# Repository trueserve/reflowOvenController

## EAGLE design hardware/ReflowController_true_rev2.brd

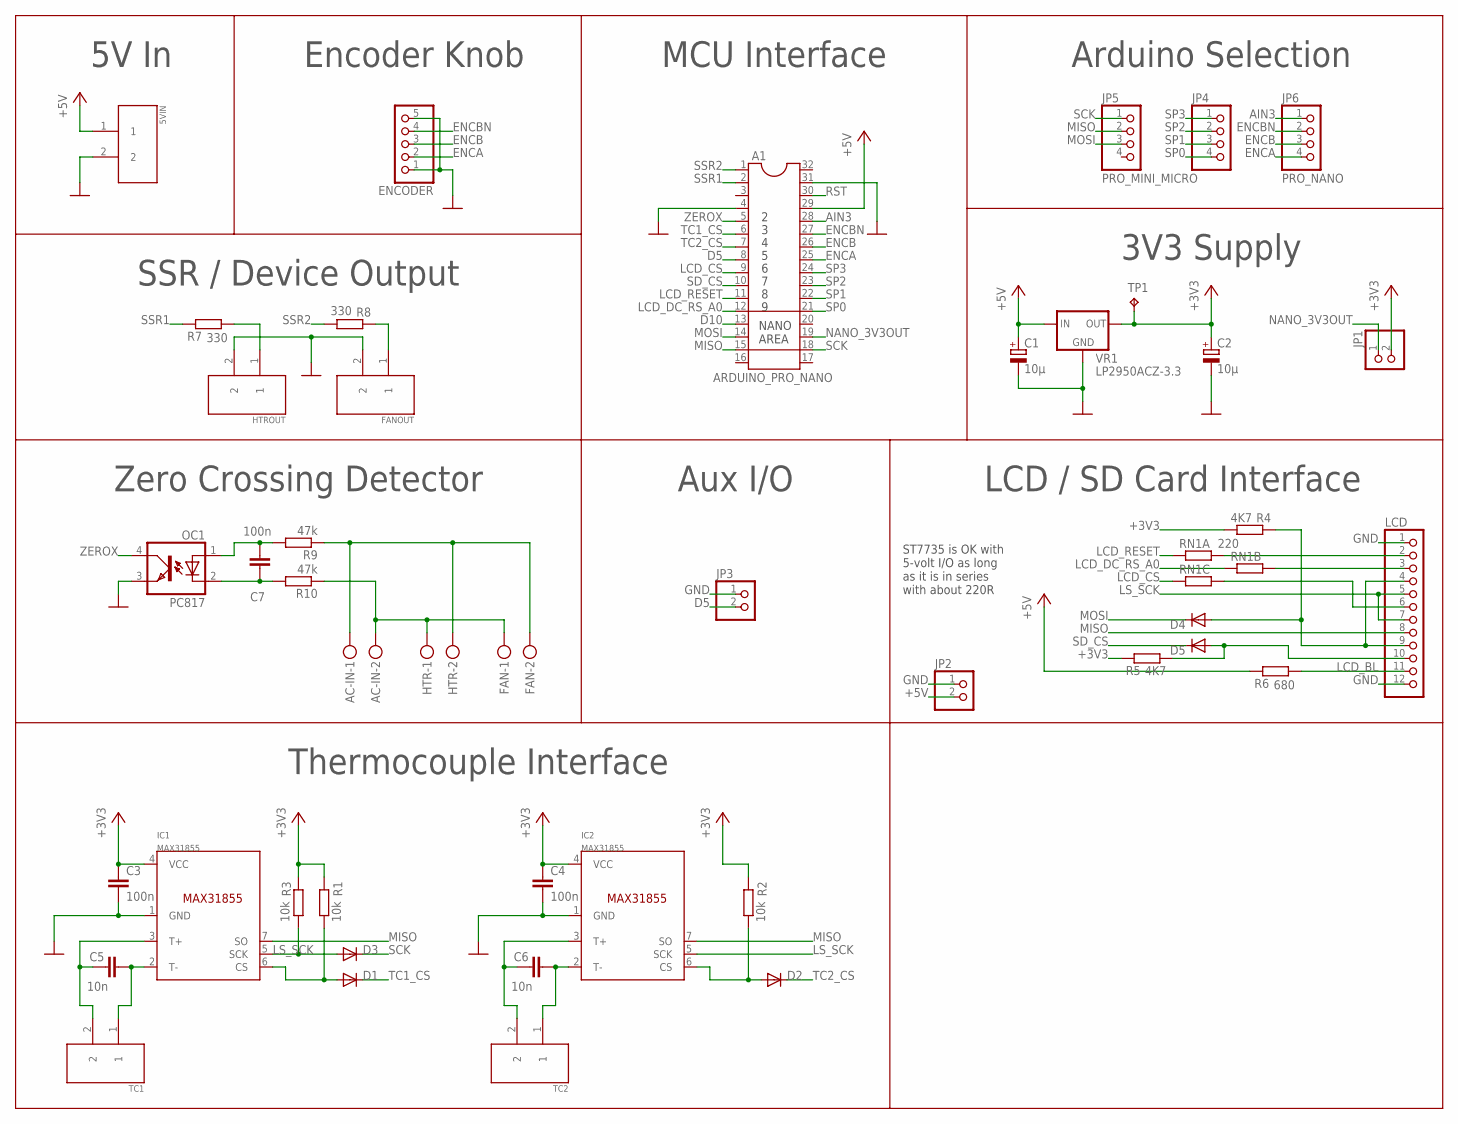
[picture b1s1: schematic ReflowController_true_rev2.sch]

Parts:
5VIN: WECO_110-M-221/2; WECO-PHOENIXTERM-2-POS
A1: ARDUINO_PRO_NANO; DIL32
AC-IN: MKDSN1,5/2-5,08
C1, C2: 10µ; C/6032-28R
C3, C4: 100n; C0805
C5, C6: 10n; C0805
C7: 100n; C150-054X183
D1, D2, D3, D4, D5: DIODESOD-123; SOD-123
ENCODER: PINHD-1X5; 1X05
FAN: MKDSN1,5/2-5,08
FANOUT: WECO_110-M-221/2; WECO-PHOENIXTERM-2-POS
HTR: MKDSN1,5/2-5,08
HTROUT: WECO_110-M-221/2; WECO-PHOENIXTERM-2-POS
IC1, IC2: MAX31855; SOIC8
JP1, JP2, JP3: PINHD-1X2; 1X02
JP4: PINHD-1X4RND; 1X04_RND
JP5: PRO_MINI_MICRO; 1X04_RND
JP6: PRO_NANO; 1X04_RND
LCD: PINHD-1X12; 1X12
OC1: PC817; DIL04
R1, R2, R3: 10k; R0805
R4, R5: 4K7; R0805
R6: 680; R0805
R7, R8: 330; R0805
R9, R10: 47k; 0207/5V
RN1: 220; RN8P-4R-CRA06S
TC1, TC2: WECO_110-M-221/2; WECO-PHOENIXTERM-2-POS
TP1: TPTP08R; TP08R
VR1: LP2950ACZ-3.3; TO92

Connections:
+3V3: C2.+, C3.1, C4.1, IC1.4 (VCC), IC2.4 (VCC), JP1.2, R1.2, R2.2, R3.2, R4.1, R5.2, TP1.TP, VR1.1 (OUT)
+5V: 5VIN.1, A1.29, C1.+, JP2.2, R6.2, VR1.3 (IN)
AC1: AC-IN.1, FAN.2, HTR.2, R9.1
AC2: AC-IN.2, FAN.1, HTR.1, R10.1
AIN3: A1.28, JP6.1
D5: A1.8, JP3.2
D10: A1.13
ENCA: A1.25, ENCODER.2, JP6.4
ENCB: A1.26, ENCODER.3, JP6.3
ENCBN: A1.27, ENCODER.4, JP6.2
GND: 5VIN.2, A1.4, A1.31, C1.-, C2.-, C3.2, C4.2, ENCODER.1, ENCODER.5, FANOUT.2, HTROUT.2, IC1.1 (GND), IC2.1 (GND), JP2.1, JP3.1, LCD.1, LCD.12, OC1.3 (EMIT), VR1.2 (GND)
LCD_BL: LCD.11, R6.1
LCD_CS: A1.9, RN1.3 (1)
LCD_DC_RS_A0: A1.12, RN1.2 (1)
LCD_RESET: A1.11, RN1.1
LS_MOSI: D4.A, LCD.4, LCD.9, R4.2
LS_SCK: D3.A, IC1.5 (SCK), IC2.5 (SCK), LCD.5, LCD.7, R3.1
LS_SD_CS: D5.A, LCD.10, R5.1
MISO: A1.15, IC1.7 (SO), IC2.7 (SO), JP5.2, LCD.8
MOSI: A1.14, D4.C, JP5.3
unnamed: C5.2, IC1.2 (T-), TC1.1
unnamed: C6.2, IC2.2 (T-), TC2.1
unnamed: C6.1, IC2.3 (T+), TC2.2
unnamed: LCD.3, RN1.7 (2)
unnamed: LCD.6, RN1.6 (2)
unnamed: C7.2, OC1.1 (A), R9.2
unnamed: LCD.2, RN1.8 (2)
unnamed: C7.1, OC1.2 (C), R10.2
unnamed: C5.1, IC1.3 (T+), TC1.2
unnamed: D2.A, IC2.6 (CS), R2.1
unnamed: D1.A, IC1.6 (CS), R1.1
NANO_3V3OUT: A1.19, JP1.1
RST: A1.30
SCK: A1.18, D3.C, JP5.1
SD_CS: A1.10, D5.C
SP0: A1.21, JP4.4
SP1: A1.22, JP4.3
SP2: A1.23, JP4.2
SP3: A1.24, JP4.1
SSR1: A1.2, R7.2
SSR1OUT: HTROUT.1, R7.1
SSR2: A1.1, R8.1
SSR2_OUT: FANOUT.1, R8.2
TC1_CS: A1.6, D1.C
TC2_CS: A1.7, D2.C
ZEROX: A1.5, OC1.4 (COL)

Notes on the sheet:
NANO AREA
MCU Interface
Arduino Selection
3V3 Supply
5V In
Encoder Knob
LCD / SD Card Interface
SSR / Device Output
Zero Crossing Detector
Aux I/O
Thermocouple Interface
ST7735 is OK with 5-volt I/O as long as it is in series with about 220R

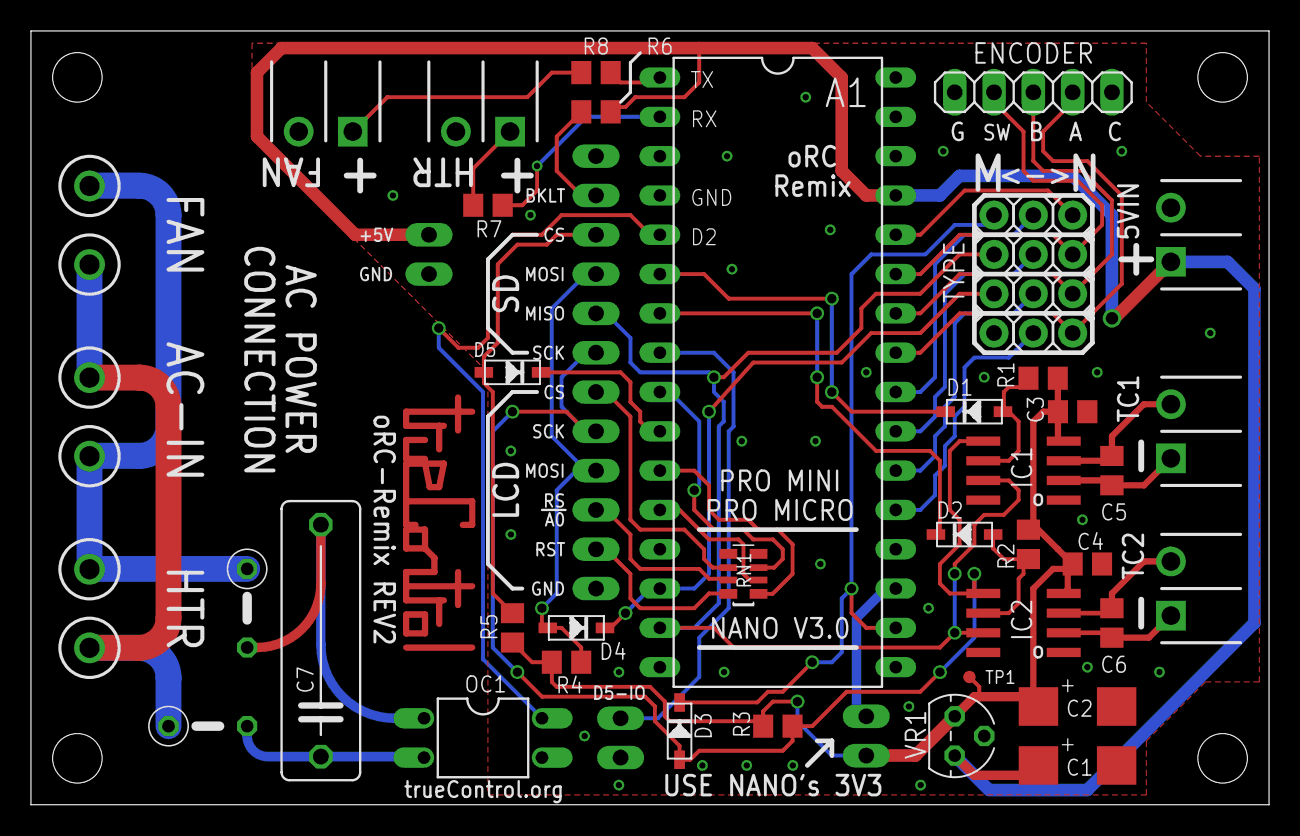
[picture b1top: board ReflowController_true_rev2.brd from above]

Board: 2 copper layers, 80.0 x 50.0 mm, 46 parts (0 on the bottom side), 44 nets.

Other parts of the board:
U$1: TC_LOGO

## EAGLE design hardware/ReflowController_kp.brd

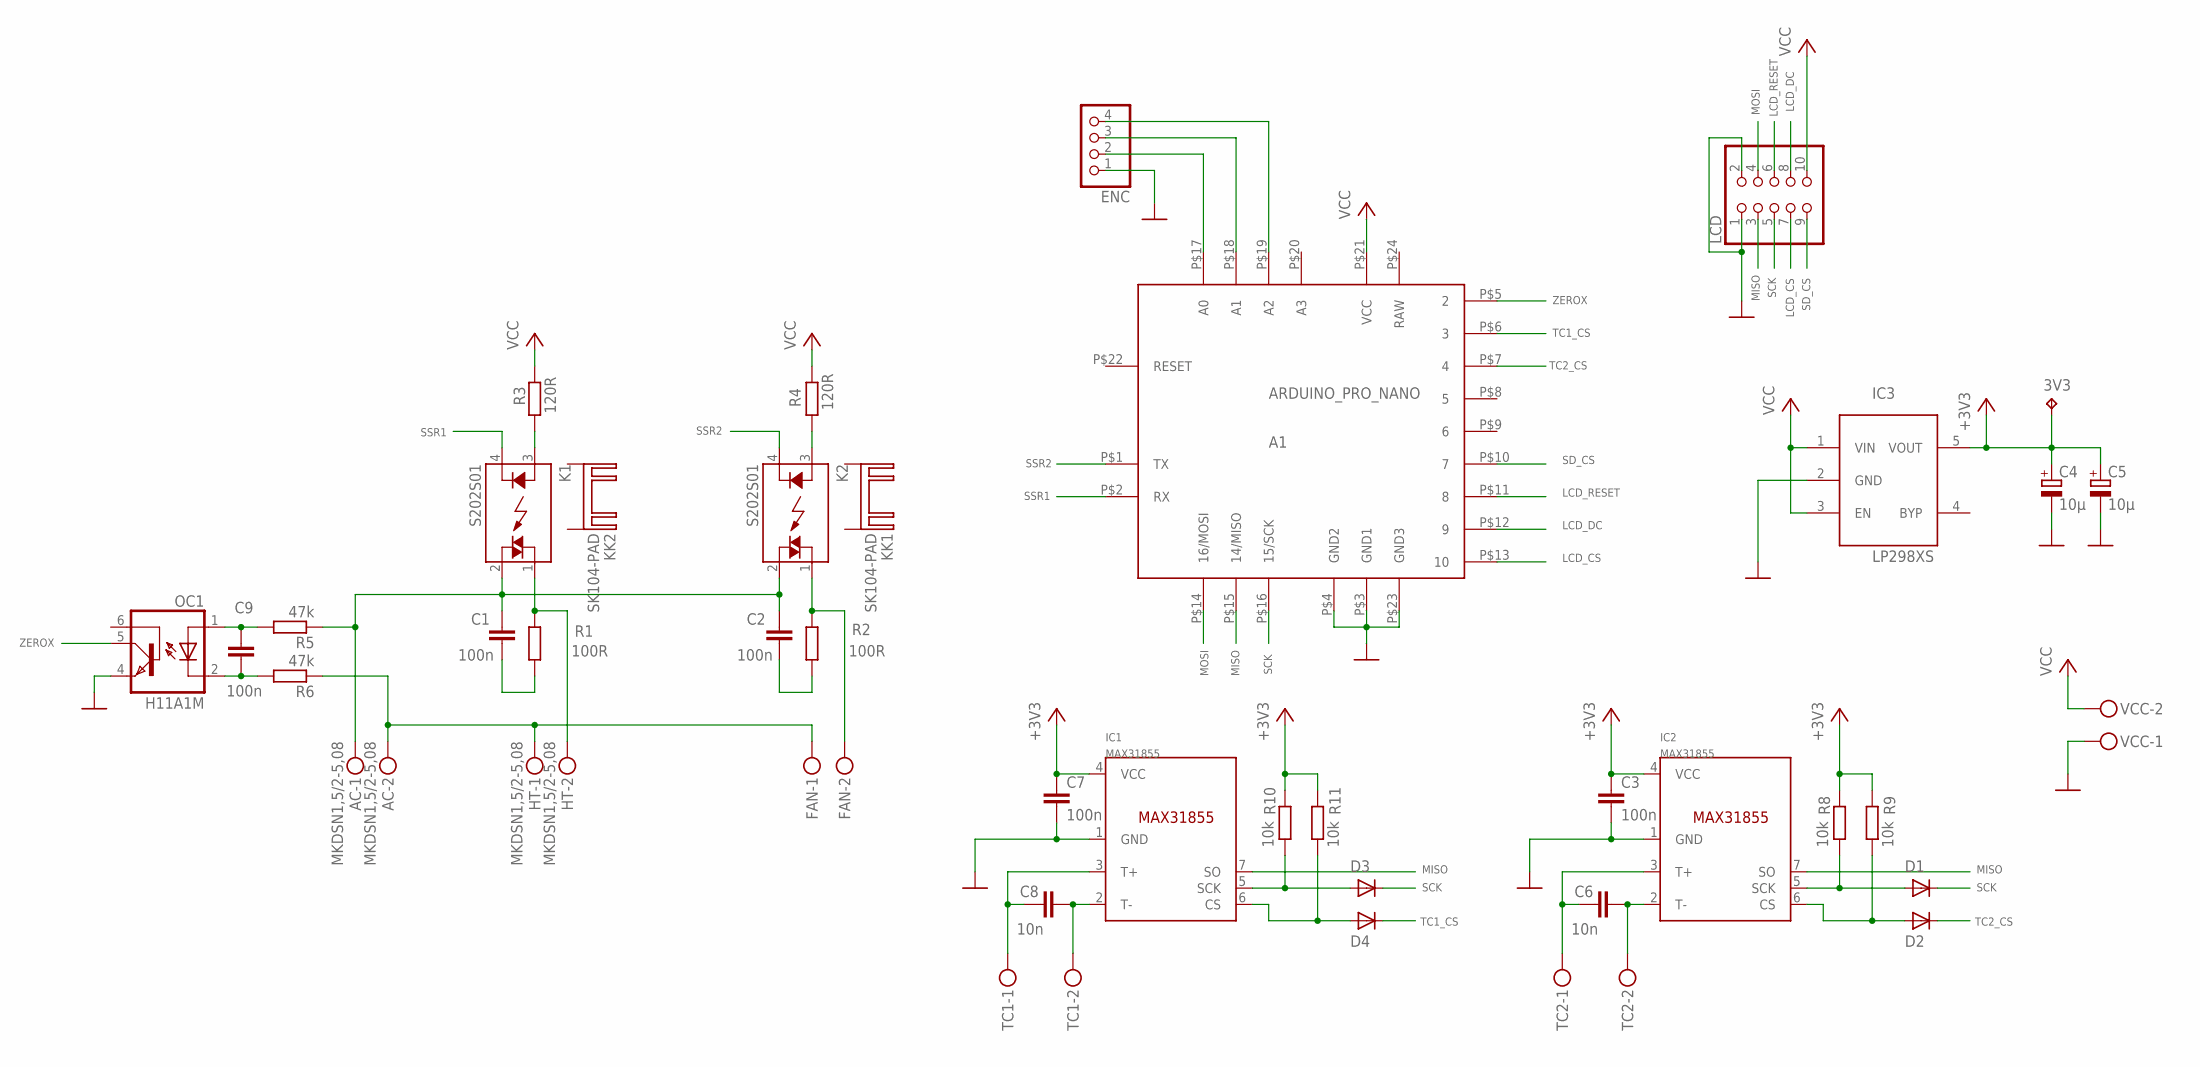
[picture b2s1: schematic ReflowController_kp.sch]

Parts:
3V3: TPTP08R; TP08R
A1: ARDUINO_PRO_NANO
AC: MKDSN1,5/2-5,08
C1, C2: 100n; XC10B5
C3, C7: 100n; C0805
C4, C5: 10µ; C/6032-28R
C6, C8: 10n; C0603
C9: 100n; C025-025X050
D1, D2, D3, D4: DIODESOD-123; SOD-123
ENC: PINHD-1X4; 1X04
FAN: MKDSN1,5/2-5,08
HT: MKDSN1,5/2-5,08
IC1, IC2: MAX31855; SOIC8
IC3: LP298XS; SOT23-5L
K1, K2: S202S01; S102S01
KK1, KK2: SK104-PAD
LCD: PINHD-2X5; 2X05
OC1: H11A1M; DIL06
R1, R2: 100R; 0207/5V
R3, R4: 120R; R0603
R5, R6: 47k; 0207/5V
R8, R9, R10, R11: 10k; R0603
TC1, TC2: MKDSN1,5/2-5,08
VCC: MKDSN1,5/2-5,08

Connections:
+3V3: 3V3.TP, C3.1, C4.+, C5.+, C7.1, IC1.4 (VCC), IC2.4 (VCC), IC3.5 (VOUT), R8.2, R9.2, R10.2, R11.2
AC1: AC.1, C1.1, C2.1, K1.2 (DS2), K2.2 (DS2), R5.1
AC2: AC.2, FAN.1, HT.1, R6.1
AC_OUT1: HT.2, K1.1 (DS1), R1.2
AC_OUT2: FAN.2, K2.1 (DS1), R2.2
GND: A1.P$3 (GND1), A1.P$4 (GND2), A1.P$23 (GND3), C3.2, C4.-, C5.-, C7.2, ENC.1, IC1.1 (GND), IC2.1 (GND), IC3.2 (GND), LCD.1, LCD.2, OC1.4 (EMI), VCC.1
LCD_CS: A1.P$13 (10), LCD.7
LCD_DC: A1.P$12 (9), LCD.8
LCD_RESET: A1.P$11 (8), LCD.6
MISO: A1.P$15 (14/MISO), IC1.7 (SO), IC2.7 (SO), LCD.3
MOSI: A1.P$14 (16/MOSI), LCD.4
unnamed: C8.2, IC1.2 (T-), TC1.2
unnamed: C6.2, IC2.2 (T-), TC2.2
unnamed: C6.1, IC2.3 (T+), TC2.1
unnamed: A1.P$17 (A0), ENC.2
unnamed: A1.P$18 (A1), ENC.3
unnamed: C1.2, R1.1
unnamed: C2.2, R2.1
unnamed: A1.P$19 (A2), ENC.4
unnamed: C9.1, OC1.1 (A), R5.2
unnamed: C9.2, OC1.2 (C), R6.2
unnamed: C8.1, IC1.3 (T+), TC1.1
unnamed: K1.3 (A), R3.2
unnamed: K2.3 (A), R4.2
unnamed: D2.A, IC2.6 (CS), R9.1
unnamed: D1.A, IC2.5 (SCK), R8.1
unnamed: D4.A, IC1.6 (CS), R11.1
unnamed: D3.A, IC1.5 (SCK), R10.1
RAW: A1.P$24 (RAW)
SCK: A1.P$16 (15/SCK), D1.C, D3.C, LCD.5
SD_CS: A1.P$10 (7), LCD.9
SSR1: A1.P$2 (RX), K1.4 (K)
SSR2: A1.P$1 (TX), K2.4 (K)
TC1_CS: A1.P$6 (3), D4.C
TC2_CS: A1.P$7 (4), D2.C
VCC: A1.P$21 (VCC), IC3.1 (VIN), IC3.3 (EN), LCD.10, R3.1, R4.1, VCC.2
ZEROX: A1.P$5 (2), OC1.5 (COL)

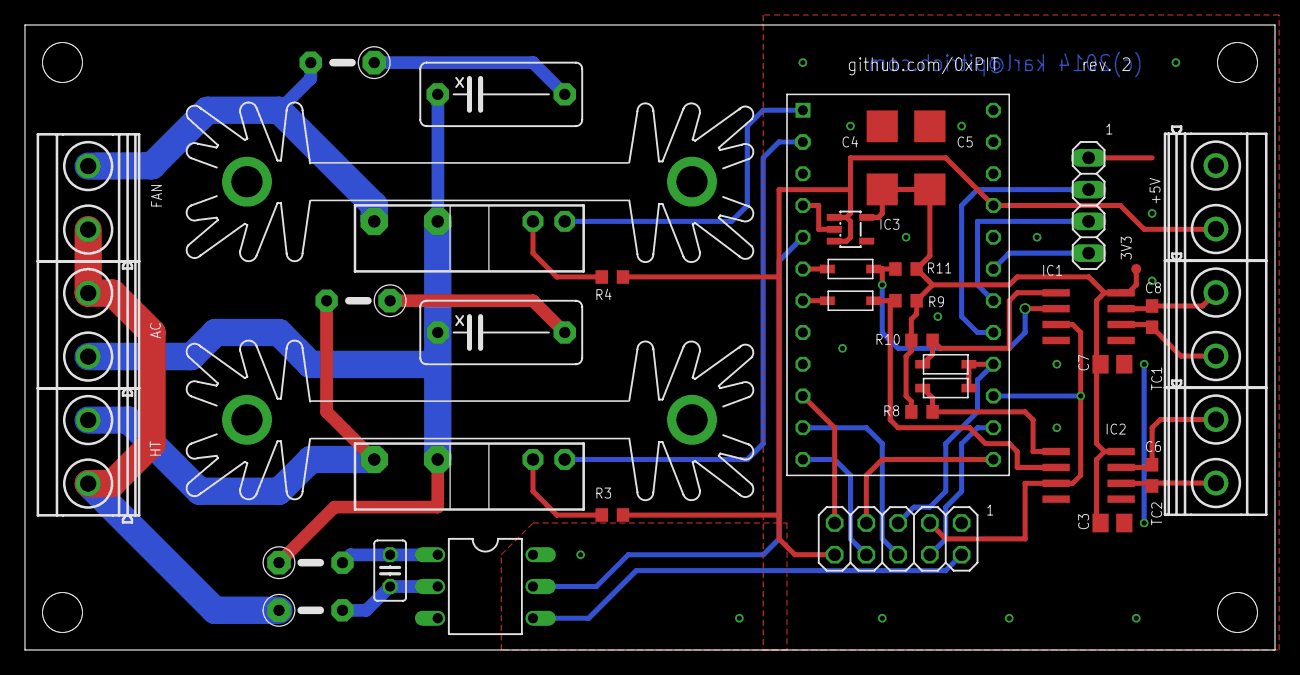
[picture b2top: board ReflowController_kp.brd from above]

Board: 2 copper layers, 100.0 x 50.0 mm, 41 parts (0 on the bottom side), 36 nets.

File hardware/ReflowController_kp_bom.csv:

Part,Value,Device,Package,Description
A1,ARDUINO_PRO_NANO,ARDUINO_PRO_NANO,ARDUINO_PRO_NANO,SparkFun Arduino Pro Nano
C1,100n,CXXC10B5,XC10B5,X CAPACITOR
C2,100n,CXXC10B5,XC10B5,X CAPACITOR
C3,100n,C-EUC0805,C0805,CAPACITOR. European symbol
C4,10µ,CPOL-EUC/6032-28R,C/6032-28R,POLARIZED CAPACITOR. European symbol
C5,10µ,CPOL-EUC/6032-28R,C/6032-28R,POLARIZED CAPACITOR. European symbol
C6,10n,C-EUC0603,C0603,CAPACITOR. European symbol
C7,100n,C-EUC0805,C0805,CAPACITOR. European symbol
C8,10n,C-EUC0603,C0603,CAPACITOR. European symbol
C9,100n,C-EU025-025X050,C025-025X050,CAPACITOR. European symbol
D1,1N4148,DIODESOD-123,SOD-123,Diode
D2,1N4148,DIODESOD-123,SOD-123,Diode
D3,1N4148,DIODESOD-123,SOD-123,Diode
D4,1N4148,DIODESOD-123,SOD-123,Diode
IC1,MAX31855,MAX31855,SOIC8,
IC2,MAX31855,MAX31855,SOIC8,
IC3,LP298XS,LP298XS,SOT23-5L,
K1,S202S01,S202S01,S102S01,Low Height Type Solid State Relays SHARP
K2,S202S01,S202S01,S102S01,Low Height Type Solid State Relays SHARP
KK1,SK104-PAD,SK104-PAD,SK104-PAD,HEATSINK manufacturer Fischer/distributor Buerklin
KK2,SK104-PAD,SK104-PAD,SK104-PAD,HEATSINK manufacturer Fischer/distributor Buerklin
OC1,H11A1M,H11A1M,DIL06,General Purpose 6-Pin Phototransistor Optocouplers
R1,100R,R-EU_0207/5V,0207/5V,RESISTOR. European symbol
R2,100R,R-EU_0207/5V,0207/5V,RESISTOR. European symbol
R3,120R,R-EU_R0603,R0603,RESISTOR. European symbol
R4,120R,R-EU_R0603,R0603,RESISTOR. European symbol
R5,47k,R-EU_0207/5V,0207/5V,RESISTOR. European symbol
R6,47k,R-EU_0207/5V,0207/5V,RESISTOR. European symbol
R8,10k,R-EU_R0603,R0603,RESISTOR. European symbol
R9,10k,R-EU_R0603,R0603,RESISTOR. European symbol
R10,10k,R-EU_R0603,R0603,RESISTOR. European symbol
R11,10k,R-EU_R0603,R0603,RESISTOR. European symbol
AC,MKDSN1.5/2-5.08,MKDSN1.5/2-5.08,MKDSN1.5/2-5.08,MKDSN 1.5/ 2-5.08 Printklemme
FAN,MKDSN1.5/2-5.08,MKDSN1.5/2-5.08,MKDSN1.5/2-5.08,MKDSN 1.5/ 2-5.08 Printklemme
HT,MKDSN1.5/2-5.08,MKDSN1.5/2-5.08,MKDSN1.5/2-5.08,MKDSN 1.5/ 2-5.08 Printklemme
TC1,MKDSN1.5/2-5.08,MKDSN1.5/2-5.08,MKDSN1.5/2-5.08,MKDSN 1.5/ 2-5.08 Printklemme
TC2,MKDSN1.5/2-5.08,MKDSN1.5/2-5.08,MKDSN1.5/2-5.08,MKDSN 1.5/ 2-5.08 Printklemme
VCC,MKDSN1.5/2-5.08,MKDSN1.5/2-5.08,MKDSN1.5/2-5.08,MKDSN 1.5/ 2-5.08 Printklemme
ENC,,PINHD-1X4,1X04,PIN HEADER
LCD,,PINHD-2X5,2X05,PIN HEADER

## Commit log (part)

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2014-10-25 Rename ReflowController.pde to ReflowController.ino
    Using extension Arduino 1.5.x GUI expects to see.
2014-10-25 Initial minor cleanup, clarification
    - Began cleaning up parts of the code and organizing sections to make it
    easier to read, no actual changes performed
    - Added ARDUINO_TYPE and BOARD_TYPE preprocessor options to configure
    the code to the target
2014-10-25 Add compile-time LCD rotation setting, usability fixes
    - Adds rotation support for LCD, and fixes text and graphics to make
    this happen
    - Adds define for rotary encoder steps at top of file
    - Fixed bug of redefine of LCD_CS in temperature.h
    - Menu items are the correct width in either rotation; editing
    - Improved splash screen, though flash size is bigger as a result
2014-10-25 Register accesses changed to Arduinoisms (portability), more clarifications
    - Minor formatting updates to fix inconsistencies and make code match
    the original programming style
    - Moved LCD physical configuration defines out of the user configurable
    area; these are set by the compile time user-configurable LCD rotation
    - Made any direct port register code no longer directly access the port
    direction and output registers. Code should be fully portable between
2014-10-26 hardware/ directory cleanup
    - Cleaned up kp's design files and documents
    - Removed kp's board house DRU, added ignore for .dru
2014-10-26 true's Reflow Controller PCB+Schematic
    My version of the Reflow Controller.
    This is REV2, untested. I have mostly tested REV1 so far. Yes, it is way
    more complicated than the original. :)
    - Schematic cleaned up and organized. Hopefully this is easier to read
    now.
    - Supports physically Arduino Pro Mini, Pro Micro or Nano V3.0
2014-10-26 Update .gitignore
    Ignore gerbers
2014-10-26 Simplify pin output control on heater, fan channels
    Since we're hardcoded to two different methods of control for the heater
    and fan, and there is no loop, there's no reason we can't just use the
    pins for the heater and fan directly. So I do this now. Saves >150bytes.
2014-10-26 Fix profile load/save can't exit; Made reset harder
    - Fixes the bug where you can't cancel loading or saving a profile, or
    cancel factory resetting
    - Makes factory resetting more difficult by requiring a double-click to
    confirm
2014-10-26 Make numeric editing text fit in vertical mode
2014-10-26 Fix double-click on root items clears the screen
    I made this bug in 425764eb29, oops
2014-10-26 Updated ReflowController/todo.txt
    - Marked off completed items
    - Explained some uncompleted items
    - Added more items
2014-10-26 TimerThree replaced with Timer2, fake_hw fixes
    Arduino Mini and Nano does not have TimerThree.
    Using Timer2 for fake hardware support.
    Fixed various issues when running in FAKE_HW mode. Saved space where
    possible in FAKE_HW mode to make room to put other things in to test.
    Hardware startup order changed to make more sense.
    Double-clicking on not previously activated Factory Reset option will no
2014-10-26 Re-added Timer3 for Micro, removed ARDUINO_TYPE
    TimerThree was re-added since the Micro doesn't have Timer2. However,
    TimerThree has a bug where it doesn't check to see if the processor is
    capable, and either Arduino or the compiler is too stupid to see that
    this isn't included anymore after the preprocessor, so either comment
    the include out or modify TimerThree to check this.
    Removed ARDUINO_TYPE and perform tasks depending on the type of
2014-10-26 Fixed time elapsed for 60Hz systems
    The time counter was set at fixed 100Hz ZX; this is now computed based
    on LINE_FREQ and now has a proper time elapsed counter.
    Timer2 and TimerThree stuff was changed / fixed so this works as
    expected in FAKE_HW mode.
2014-10-26 Fix bottom status bar being cut off
2014-10-26 Added vertical mode graph display screen
    Still need to optimize; the changes and centering code add ~160 bytes to
    the compiled size.
2014-10-27 Optional support to store text strings in Flash
    RAM likely won't run short on this project, but a macro has been added
    wrapping all text, which as an example can be used as the Arduino F(x)
    macro.
    Also changed idleTemp to a defined value; this saved ~50bytes of Flash.
    TFT_ defines are now LCD_ defines.
    Need to look into why space is a consistent ~70 bytes higher when using
2014-10-27 Fixed garbage when editing digits of variable size
    If the amount of digits changed when editing something, such as fan
    speed, garbage would be left behind. Smallest hack I could find just
    prints some spaces at the end.
2014-10-27 Changed some const to #defines
    Saves 6 bytes. =)
2014-10-27 Remove stale edit / information text, update todo.txt
    After editing an item (fan speed, PID values, etc) the informational
    text would be left behind on the bottom of the screen. I fix this by
    drawing a rectangle.
    Adding this code saved 82 bytes of space, I need to know why.
    Updated todo.txt with completed tasks marked off, more tasks to complete
    added
2014-10-27 Show how to exit submenus while in submenus
    Most of the time the oven is just configured, profiles loaded and run,
    so this serves two purposes: remind someone who hardly edits anything
    how to exit a menu, and teach those new to the unit how to exit a menu.
2014-10-27 Fix bad click to exit description
    When editing in a submenu, if you double-click to attempt to exit, it
    does so but one would assume the change wouldn't save. The editing
    applies all changes immediately so this isn't the case. Reworked the
    menus to not show this text.
2014-10-28 Splash text change; code consistency
2014-10-29 Fixed submenu scrolling turning exit text blue
2014-10-29 Show profile ID; fix load profile shows wrong ID
2014-10-29 Using <avr/eeprom.h> over EEPROM.h
    The code already makes use of <avr/eeprom.h> so why not use it
    everywhere? Simplifies code a bit, and I would like to use eeprom_*_word
    so here is the change. Saves ~40 bytes.
    Changed the location of various variables to the end of EEPROM rather
    than right after the profiles. If the profile count changes in firmware,
    it won't put garbage in these variables anymore.
2014-10-29 Updated todo.txt
2014-10-29 Clarified new EEPROM offsets, new profile defaults
    The old offsets were pretty shit; hopefully these are clearer. Gaps are
    for future options I still need to implement though it really doesn't
    matter where they go.
    Set the profile defaults to what I will be using during development.
    Saved 6 bytes removing heaterPID startup values that aren't used.
2014-10-29 Removed per-profile checksum; added global checksum
    This project doesn't need per-profile checksums. Implemented a global
    checksum to verify data, and if not valid, reset all data.
    Changed function definition formatting to be consistent.
2014-10-30 Format rampRate nicer; updated todo.txt
2014-11-02 Changed thermocouple variable name
    Changed variable A to Tc[x] to accomodate multiple thermocouples and
    make it clearer in code where the thermocouple data is being used.
2014-11-02 Fixed missed thermocouple variable names
2014-11-02 Changed PIDTune fixed variables to #defines
    Some values did not need to be variables, so have been changed to save
    space.
2014-11-02 Simplified getItemValuePointer, rampRate now int16_t
    getItemValuePointer was used to recall various values for display and
    editing. It did so by updating indirect ptr for a double and an int16.
    The function was changed instead to return pointer to type void, which
    simplifies use and lets any time be used where necessary.
    rampUpRate and rampDownRate are now int16_t and are stored as tenths of
    a degree. The overhead for doing math to print these for editing is less
2014-11-02 Support drawing lines instead of pixels in graphs
    Lines look nicer, especially when the rampdown can be sudden and it
    leaves a gap. However it takes >90 bytes of flash, so it is a
    compile-time option right now.
2014-11-02 timerIsr tick rate reduced from 10KHz to 4KHz
    For this slow MCU, a 10KHz timer ISR is just too fast - context switch /
    ISR to code execute time is pretty big on AVR so this ISR was stealing a
    lot of time just being alive. From what I can tell changing this to 4KHz
    won't really hurt anything but will improve responsiveness of the menus.
    Save 6 bytes by changing when encoder is serviced in this interrupt.
2014-11-02 Stop rendering the graph after process completes
    After the process completes, the graph code will proceed to loop around
    and print a cooled down oven line. This doesn't look good. Added option
    to stop rendering the graph as soon as we hit the Completed step.
    NOTE: This version will stop rendering everything, including
    temperature. A future version will render the current temperature when
    done.
2014-11-02 Continue updating temp when not updating graph
    Shows current oven temperature after Complete phase, which is what it
    should have done after my last change.
2014-11-02 Fix text size is wrong after complete phase
    Once the process completes, text size is stuck large, so exiting to the
    menu prints unusable items. Oops.
2014-11-03 Fixed elapsed time not showing after complete phase
    Wow, I missed a lot on this. If a completion has occurred, then the next
    cycle wouldn't have a timer. Fixed and also clarified the variable name.
2014-11-03 Cleaned up thermocouple stuff for adding second TC
2014-11-03 Show temps on graph lines, related bugfixes
    Added code to show temperatures on the graph lines, on the right-hand
    side of the graph.
    Wrote the number of bytes required to use each graph option alone.
    Removed all use of Color565() and replaced with #define'd values. Saves
    72 bytes.
    Fixed bug in stop graph on done code that failed compilation of the
2014-11-03 Minor optimizations
    Low hanging fruit by optimizing type sizes.
    Fixed some flash-related stuff that could save SRAM if ever needed in
    the future.
2014-11-03 Added menu area separator, neatened landscape view
    Added a horizontal separator to separate the menu from the lower area. I
    plan to do things in the lower area, and it also helps to visually
    identify that there may be more than 5 things in the menu.
    Darkened the bottom bar in the graph to separate the graph from the
    heater/fan/rate status info.
2015-05-16 Fixed wrong pin selection on certain micros
    When using the Mini or Nano boards, fan and heater pinout is swapped
    from the Pro Micro. Changed this to work for all boards.
2015-05-16 Revert "Fixed wrong pin selection on certain micros"
    This reverts commit 9399fe05cc75e9bc352a507ebe0795d7d5982306.
2015-05-16 Removed unnecessary startCycleZeroCrossTicks
2015-05-16 Fan control fixes
    Some fans (like mine?) won't work at lower speeds. Implemented a slower
    toggling thing to adjust fan speed.
    Also implemented fan pin invert, though I suspect 0xPIT's SSRs work
    backwards or something and I should be running in normal mode.
    I also think the phase calculation for the fan was incorrect? Changed to
    what I think it should be.
2015-05-16 Fixed the heater not working
    I broke it further in the last couple of commits, but it didn't work
    correctly anyway. It should now.
    However my power strip trips after a while when the heater is running so
    I will experiment with slower pulsed solutions.
    Added a currently non-functioning wave packet fan mode.
2015-05-16 Added pulsed heater mode
    Is there a reason for requiring wave packet? This takes less code spaces
    and causes less freakout on my electrical system.
2015-05-16 Changed MS_PER_SINE to SINES_PER_SEC
    This is really how it works in the code, and fixes 60Hz not timing
    correctly.
2015-05-16 Fixed PID not working properly
    Output was set to 0% on first run and wasn't set correctly on following
    runs. Fixed by fixing setting automatic mode in PID_v1 as well as the
    fixes in this file.
2015-05-16 Front page temperature updating at wrong times
    Also adjusted default PID settings and default reflow profile to better
    match my oven.

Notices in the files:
hardware/ReflowController_kp.brd:
(c)2014 karl@pitrich.com
